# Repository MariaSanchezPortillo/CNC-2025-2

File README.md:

# CNC

Este proyecto desarrolla una CNC casera, económica y educativa, basada en la estructura del proyecto Piccolo, pero utilizando un ESP32 y servomotores SG-5010 para lograr un sistema compacto, preciso y fácil de replicar.

## 🔧 Descripción General

La CNC opera mediante un ESP32 que controla tres servomotores, permitiendo ejecutar trazados y movimientos básicos en un pequeño plano cartesiano. Su diseño está pensado para estudiantes que desean aprender conceptos de CNC sin requerir máquinas costosas.

## 📦 Componentes Principales

- ESP32 

- Servomotores SG-5010 (x3)

- Estructura tipo Piccolo 

- Fuente de alimentación adecuada

- Cableado y accesorios básicos

## 🎯 Objetivo del Proyecto

Construir una mini CNC funcional y accesible que permita comprender el funcionamiento del control numérico, el uso de servomotores y la integración entre hardware y software.

## 🧠 Criterio de Diseño

- Bajo costo y fácil disponibilidad de piezas

- Compatibilidad con la arquitectura Piccolo

- Uso de servos SG-5010 por su mayor torque y estabilidad

- Diseño modular para ajustes y mejoras futuras

## ▶️ Funcionamiento desde el Punto de Vista del Usuario

1. Encender la máquina.

2. Conectar al ESP32 vía USB o Wi-Fi.

3. Enviar comandos simples o un archivo de trazado.

4. La CNC ejecuta los movimientos automáticamente.

5. El usuario obtiene dibujos o cortes ligeros con buena precisión.

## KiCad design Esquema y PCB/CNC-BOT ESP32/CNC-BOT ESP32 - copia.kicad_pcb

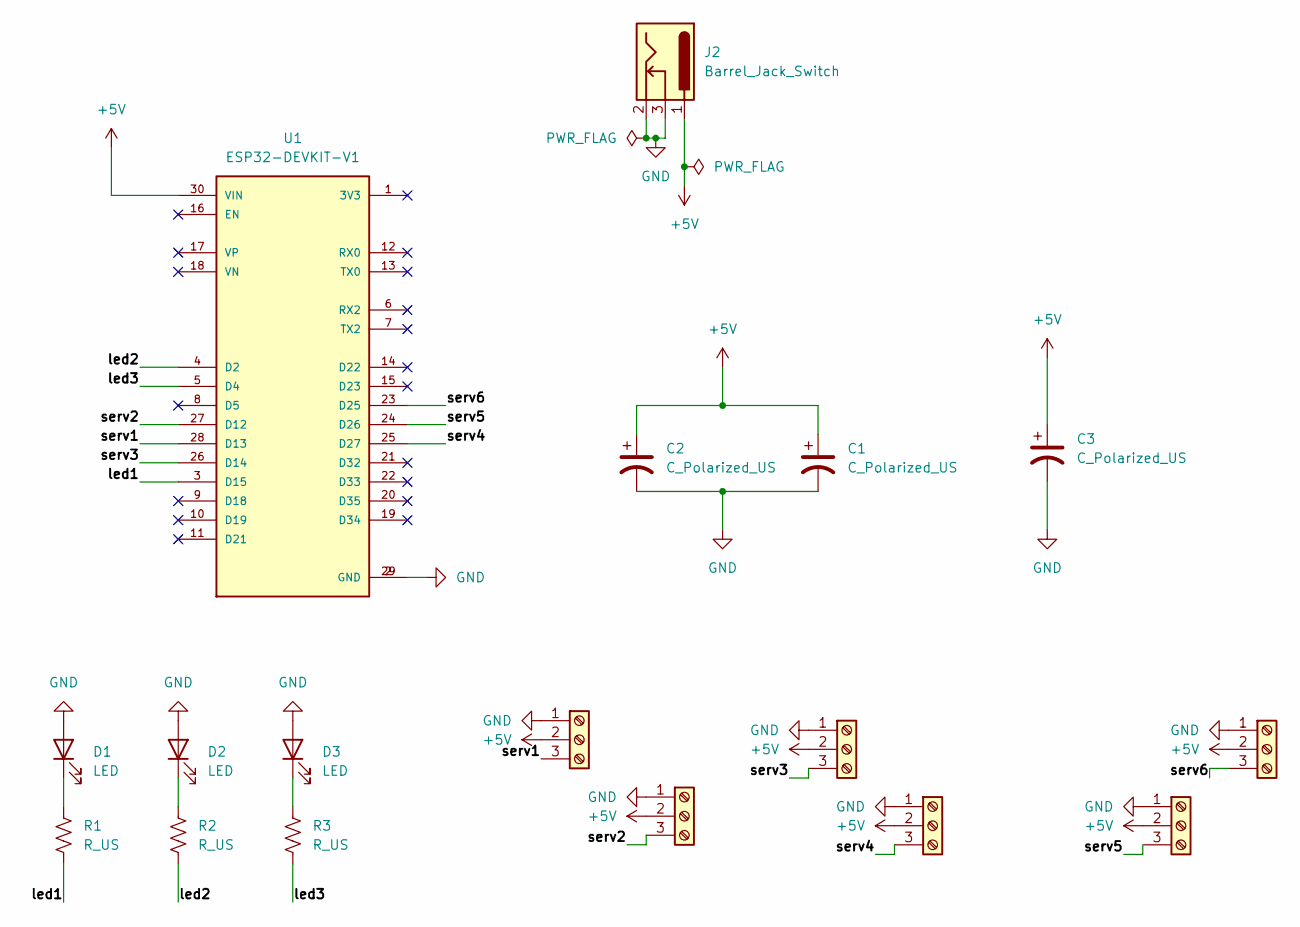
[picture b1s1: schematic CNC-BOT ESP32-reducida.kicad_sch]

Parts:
C1, C2, C3: C_Polarized_US; CP_Radial_D10.0mm_P5.00mm
D1, D2, D3: LED; LED_D3.0mm_Horizontal_O6.35mm_Z10.0mm
J2: Barrel_Jack_Switch; BarrelJack_Horizontal
J5, J6, J7, J8, J9, J10: Screw_Terminal_01x03; PinHeader_1x03_P2.54mm_Vertical
R1, R2, R3: R_US; R_Axial_DIN0207_L6.3mm_D2.5mm_P7.62mm_Horizontal
U1: ESP32-DEVKIT-V1; MODULE_ESP32_DEVKIT_V1; PARTREV N/A

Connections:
+5V: C1.1, C2.1, C3.1, J2.1, J5.2, J6.2, J7.2, J8.2, J9.2, J10.2, U1.30 (VIN)
/led1: R1.2, U1.3 (D15)
/led2: R2.2, U1.4 (D2)
/led3: R3.2, U1.5 (D4)
/serv1: J10.3, U1.28 (D13)
/serv2: J5.3, U1.27 (D12)
/serv3: J9.3, U1.26 (D14)
/serv4: J6.3, U1.25 (D27)
/serv5: J7.3, U1.24 (D26)
/serv6: J8.3, U1.23 (D25)
GND: C1.2, C2.2, C3.2, D1.2 (A), D2.2 (A), D3.2 (A), J2.2, J2.3, J5.1, J6.1, J7.1, J8.1, J9.1, J10.1, U1.2 (GND), U1.29 (GND)
unnamed: D1.1 (K), R1.1
unnamed: D2.1 (K), R2.1
unnamed: D3.1 (K), R3.1

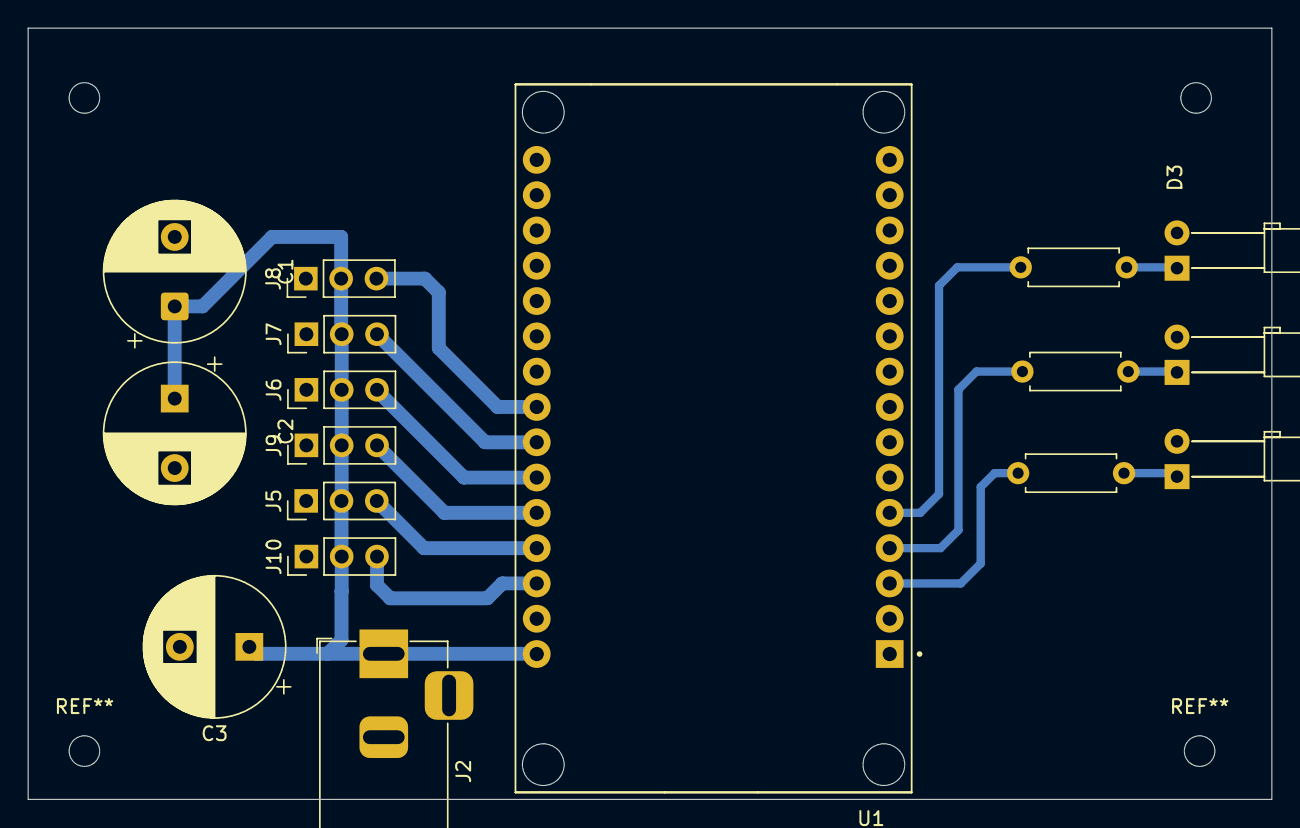
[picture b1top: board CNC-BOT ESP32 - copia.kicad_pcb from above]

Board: 2 copper layers, 89.5 x 55.5 mm, 17 parts (0 on the bottom side), 14 nets.

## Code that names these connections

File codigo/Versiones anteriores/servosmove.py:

from machine import Pin, PWM
import time
#Configuracion de Leds
led1 = Pin(15, Pin.OUT)
led2 = Pin(2, Pin.OUT)
led3 = Pin(4, Pin.OUT)

led1.value(1)

# Configuración de los servos
servo_x = PWM(Pin(14), freq=50)  # Servo X en el pin 13
servo_y = PWM(Pin(13), freq=50)  # Servo Y en el pin 14
servo_z = PWM(Pin(27), freq=50)  # Servo Z en el pin 27

# Configuración de los rangos
MIN_DUTY = 40
MAX_DUTY_XY = 135
MAX_DUTY_Z = 120

# Función para convertir grados a duty cycle para el servo X e Y
def grados_a_duty_xy(grados):
    if grados < 10:
        grados = 10
    elif grados > 170:
        grados = 170
    return MIN_DUTY + (MAX_DUTY_XY - MIN_DUTY) * (grados - 0) / 180

# Función para convertir grados a duty cycle para el servo Z
def grados_a_duty_z(grados):
    if grados < 5:
        grados = 5
    elif grados > 25:
        grados = 25
    return MIN_DUTY + (MAX_DUTY_Z - MIN_DUTY) * (grados - 0) / 180

# Función para mover el servo X
def mover_servo_x(grados):
    duty = int(grados_a_duty_xy(grados))
    servo_x.duty(duty)
    print(f"Servo X movido a {grados} grados (duty: {duty})")

# Función para mover el servo Y
def mover_servo_y(grados):
    duty = int(grados_a_duty_xy(grados))
    servo_y.duty(duty)
    print(f"Servo Y movido a {grados} grados (duty: {duty})")

# Función para mover el servo Z
def mover_servo_z(grados):
    duty = int(grados_a_duty_z(grados))
    servo_z.duty(duty)
    print(f"Servo Z movido a {grados} grados (duty: {duty})")

# Función para mover los servos a las posiciones iniciales
def posicion_inicial():
    mover_servo_z(10)  # Levantar lápiz (Z en 10 grados)
    time.sleep(0.5)
    mover_servo_x(90)# Servo X en el centro (90 grados)
    time.sleep(0.5)
    mover_servo_y(150)  # Servo Y en 170 grados
    print("Posición inicial alcanzada")
    time.sleep(1)
    
#Solicitud de posiciones
#posicion x
def solicitar_posicion_x():
    while True:
        try:
            posicion_x = int(input("Ingrese la posición X de un rango de -80  a  80: "))

            if (-80) <= posicion_x <= 80:
                print(f"Posiciones válidas: X={posicion_x}")
                return posicion_x
            else:
                print("Error: Las posiciones deben estar entre -80 y 80. Intente nuevamente.")
        except ValueError:
            print("Error: Ingrese un número válido.")
#posicion y
def solicitar_posicion_y():
    while True:
        try:
            posicion_y = int(input("Ingrese la posición Y de un rango de -80  a  80: "))

            if (-80) <= posicion_y <= 80:
                print(f"Posiciones válidas: Y={posicion_y}")
                posicion_y= -(posicion_y)
                return posicion_y
            else:
                print("Error: Las posiciones deben estar entre -80 y 80. Intente nuevamente.")
        except ValueError:
            print("Error: Ingrese un número válido.")
            
def longitud_cuadrados():
    while True:
        try:
            numero = int(input("Ingrese un número mayor que 0 y menor o igual a 80 "))
            
            # Verificamos que el número sea mayor a 0, par, y que sumado a 90 no supere 170
            if numero > 0 and numero % 2 == 0 and (numero + 90) <= 170:
                print(f"Número válido: {numero}")
                return numero
            else:
                print("Error: El número debe ser mayor a 0 y menor o igual a 80")
        except ValueError:
            print("Error: Ingrese un número válido.")

#FIGURAS
#lINEAS
def dibujar_linea():
    led2.value(1)
    print('Determine el primer punto: ')
    p_x1 = solicitar_posicion_x()
    p_y1 = solicitar_posicion_y()
    print('Determine el segundo Punto: ')
    p_x2 = solicitar_posicion_x()
    p_y2 = solicitar_posicion_y()
    time.sleep(1)
    
    led2.value(0)
    led3.value(1)
    
    mover_servo_x(90 + p_x1)
    mover_servo_y(90 + p_y1)
    time.sleep(1)
    mover_servo_z(26)
    time.sleep(1)
    mover_servo_x(90 + p_x2)
    mover_servo_y(90 + p_y2)
    time.sleep(1)
    led2.value(1)
    led3.value(0)
    posicion_inicial()
    

 
    
#Cuadrado
def cuadrado():
    mover_servo_x(90)
    time.sleep(1)
    mover_servo_y(90)
    time.sleep(1)
    longitud = longitud_cuadrados()
    mover_servo_y(90-(longitud/2))
    time.sleep(1)
    mover_servo_z(26)
    time.sleep(1)
    mover_servo_x(90+(longitud/2))
    time.sleep(1)
    mover_servo_y(90-(longitud/2)+longitud)
    time.sleep(1)
    mover_servo_x(90+(longitud/2)-longitud)
    time.sleep(1)
    mover_servo_y(90+(longitud/2)-longitud)
    time.sleep(1)
    mover_servo_x(90)
    time.sleep(1)
    posicion_inicial()
    time.sleep(1)
    
while True:
    print("¿Qué deseas hacer?")
    print("1. Dibujar una línea")
    print("2. Dibujar un cuadrado")
    eleccion = input("Elige una opción (1 o 2): ")
    
    if eleccion == "1":
        dibujar_linea()
    elif eleccion == "2":
        cuadrado()
    else:
        print("Opción no válida, intenta de nuevo.")

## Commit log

2025-12-10 README
    Added detailed project description, components, objectives, design criteria, and user operation instructions.
2025-12-13 Archivos del proyecto
    Archivos del proyecto
2025-12-13 Reformat
2025-12-13 videos
2025-12-13 evidencias
2025-12-13 new video
